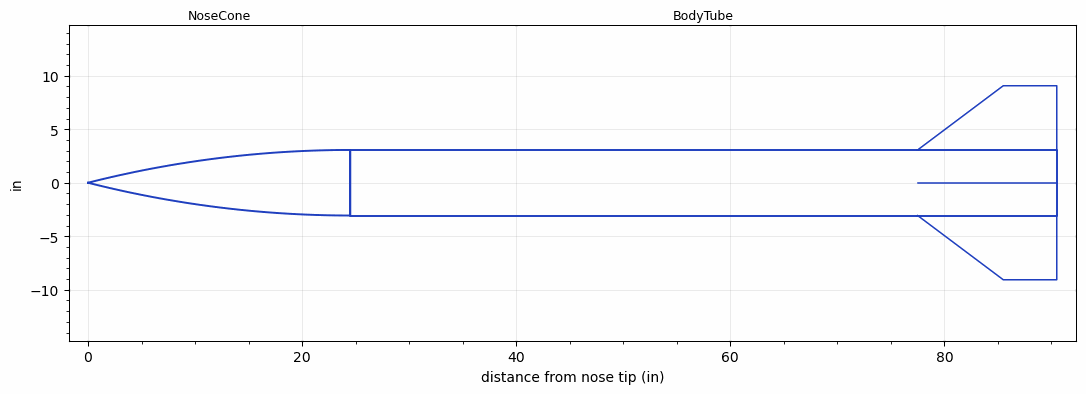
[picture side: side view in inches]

<RASAeroDocument>
 <FileVersion>2</FileVersion>
 <RocketDesign>
  <NoseCone>
   <Length>24.5</Length>
   <Diameter>6.125</Diameter>
   <Shape>Tangent Ogive</Shape>
   <Location>0</Location>
  </NoseCone>
  <BodyTube>
   <Length>66</Length>
   <Diameter>6.125</Diameter>
   <RailGuideDiameter>0.5</RailGuideDiameter>
   <RailGuideHeight>0.5</RailGuideHeight>
   <Location>24.5</Location>
   <Fin>
    <Count>4</Count>
    <Chord>13</Chord>
    <Span>6</Span>
    <SweepDistance>8</SweepDistance>
    <TipChord>5</TipChord>
    <Thickness>0.5</Thickness>
    <Location>13</Location>
    <AirfoilSection>Hexagonal</AirfoilSection>
    <FX1>0.5</FX1>
    <FX3>0.25</FX3>
   </Fin>
  </BodyTube>
  <Surface>Smooth (Zero Roughness)</Surface>
  <ModifiedBarrowman>False</ModifiedBarrowman>
  <Turbulence>False</Turbulence>
  <UseBooster1>False</UseBooster1>
  <UseBooster2>False</UseBooster2>
 </RocketDesign>
 <LaunchSite>
  <Altitude>4000</Altitude>
  <Pressure>0</Pressure>
  <RodAngle>2</RodAngle>
  <RodLength>17</RodLength>
  <Temperature>90</Temperature>
  <WindSpeed>0</WindSpeed>
 </LaunchSite>
 <Recovery>
  <Altitude1>1000</Altitude1>
  <Altitude2>1000</Altitude2>
  <DeviceType1>None</DeviceType1>
  <DeviceType2>None</DeviceType2>
  <Event1>False</Event1>
  <Event2>False</Event2>
  <Size1>1</Size1>
  <Size2>1</Size2>
  <EventType1>None</EventType1>
  <EventType2>None</EventType2>
  <CD1>1.33</CD1>
  <CD2>1.33</CD2>
 </Recovery>
 <SimulationList>
  <Simulation>
   <SustainerEngine>M2400T  (AT)</SustainerEngine>
   <SustainerLaunchWt>60</SustainerLaunchWt>
   <SustainerNozzleDiameter>1</SustainerNozzleDiameter>
   <SustainerCG>58</SustainerCG>
   <SustainerIgnitionDelay>0</SustainerIgnitionDelay>
   <Booster1SeparationDelay>0</Booster1SeparationDelay>
   <Booster1IgnitionDelay>0</Booster1IgnitionDelay>
   <IncludeBooster1>False</IncludeBooster1>
   <Booster2Delay>0</Booster2Delay>
   <IncludeBooster2>False</IncludeBooster2>
   <TimetoApogee>24.51047</TimetoApogee>
   <MaxAltitude>9489.014</MaxAltitude>
   <MaxVelocity>846.4393</MaxVelocity>
   <OptimumWt>36</OptimumWt>
   <OptimumMaxAlt>36</OptimumMaxAlt>
  </Simulation>
  <Simulation>
   <SustainerEngine>M1297W  (AT)</SustainerEngine>
   <SustainerLaunchWt>60</SustainerLaunchWt>
   <SustainerNozzleDiameter>1</SustainerNozzleDiameter>
   <SustainerCG>58</SustainerCG>
   <SustainerIgnitionDelay>0</SustainerIgnitionDelay>
   <Booster1SeparationDelay>0</Booster1SeparationDelay>
   <Booster1IgnitionDelay>0</Booster1IgnitionDelay>
   <IncludeBooster1>False</IncludeBooster1>
   <Booster2Delay>0</Booster2Delay>
   <IncludeBooster2>False</IncludeBooster2>
   <TimetoApogee>25</TimetoApogee>
   <MaxAltitude>10322</MaxAltitude>
   <MaxVelocity>889</MaxVelocity>
  </Simulation>
  <Simulation>
   <SustainerEngine>M1315W  (AT)</SustainerEngine>
   <SustainerLaunchWt>60</SustainerLaunchWt>
   <SustainerNozzleDiameter>1</SustainerNozzleDiameter>
   <SustainerCG>58</SustainerCG>
   <SustainerIgnitionDelay>0</SustainerIgnitionDelay>
   <Booster1SeparationDelay>0</Booster1SeparationDelay>
   <Booster1IgnitionDelay>0</Booster1IgnitionDelay>
   <IncludeBooster1>False</IncludeBooster1>
   <Booster2Delay>0</Booster2Delay>
   <IncludeBooster2>False</IncludeBooster2>
   <TimetoApogee>23</TimetoApogee>
   <MaxAltitude>7601</MaxAltitude>
   <MaxVelocity>656</MaxVelocity>
  </Simulation>
  <Simulation>
   <SustainerEngine>M1850W  (AT)</SustainerEngine>
   <SustainerLaunchWt>60</SustainerLaunchWt>
   <SustainerNozzleDiameter>1</SustainerNozzleDiameter>
   <SustainerCG>58</SustainerCG>
   <SustainerIgnitionDelay>0</SustainerIgnitionDelay>
   <Booster1SeparationDelay>0</Booster1SeparationDelay>
   <Booster1IgnitionDelay>0</Booster1IgnitionDelay>
   <IncludeBooster1>False</IncludeBooster1>
   <Booster2Delay>0</Booster2Delay>
   <IncludeBooster2>False</IncludeBooster2>
   <TimetoApogee>24</TimetoApogee>
   <MaxAltitude>9226</MaxAltitude>
   <MaxVelocity>741</MaxVelocity>
  </Simulation>
  <Simulation>
   <SustainerEngine>M1419W  (AT)</SustainerEngine>
   <SustainerLaunchWt>60</SustainerLaunchWt>
   <SustainerNozzleDiameter>1</SustainerNozzleDiameter>
   <SustainerCG>58</SustainerCG>
   <SustainerIgnitionDelay>0</SustainerIgnitionDelay>
   <Booster1SeparationDelay>0</Booster1SeparationDelay>
   <Booster1IgnitionDelay>0</Booster1IgnitionDelay>
   <IncludeBooster1>False</IncludeBooster1>
   <Booster2Delay>0</Booster2Delay>
   <IncludeBooster2>False</IncludeBooster2>
   <TimetoApogee>26</TimetoApogee>
   <MaxAltitude>9524</MaxAltitude>
   <MaxVelocity>731</MaxVelocity>
  </Simulation>
  <Simulation>
   <SustainerEngine>M1939W  (AT)</SustainerEngine>
   <SustainerLaunchWt>60</SustainerLaunchWt>
   <SustainerNozzleDiameter>1</SustainerNozzleDiameter>
   <SustainerCG>58</SustainerCG>
   <SustainerIgnitionDelay>0</SustainerIgnitionDelay>
   <Booster1SeparationDelay>0</Booster1SeparationDelay>
   <Booster1IgnitionDelay>0</Booster1IgnitionDelay>
   <IncludeBooster1>False</IncludeBooster1>
   <Booster2Delay>0</Booster2Delay>
   <IncludeBooster2>False</IncludeBooster2>
   <TimetoApogee>30</TimetoApogee>
   <MaxAltitude>15183</MaxAltitude>
   <MaxVelocity>1075</MaxVelocity>
  </Simulation>
 </SimulationList>
</RASAeroDocument>
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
